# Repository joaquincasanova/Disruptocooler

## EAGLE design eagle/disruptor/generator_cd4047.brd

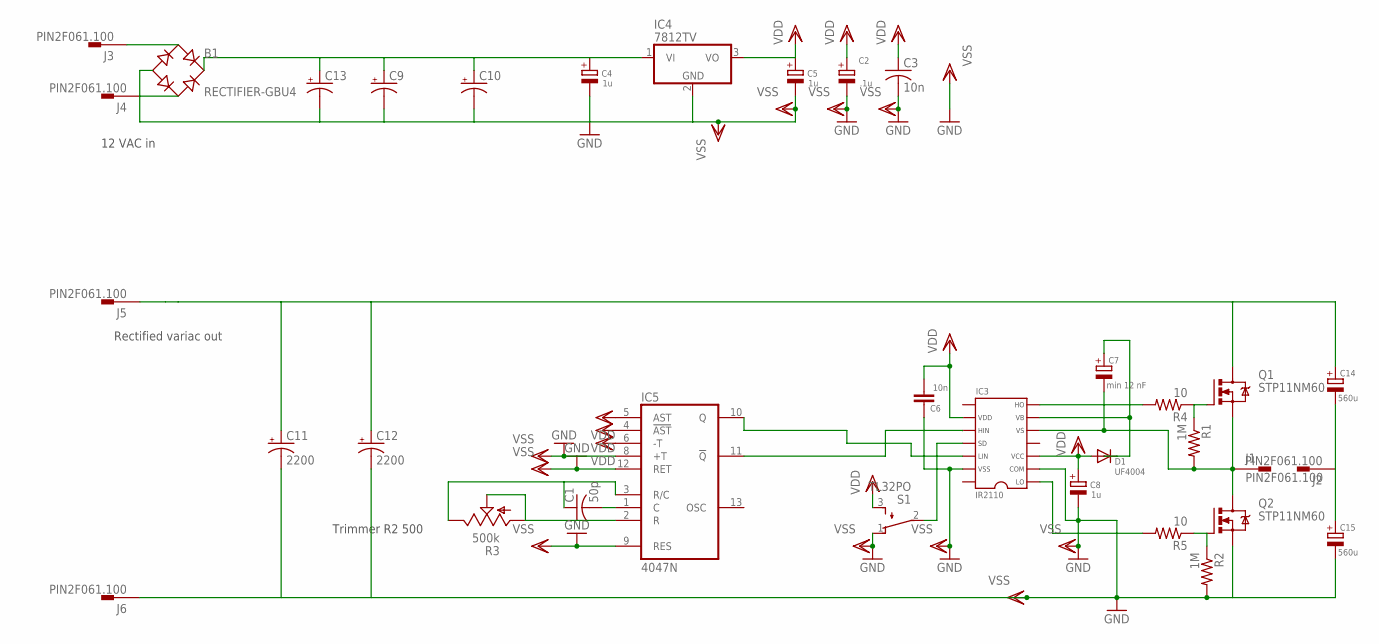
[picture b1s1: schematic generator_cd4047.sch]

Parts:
B1: RECTIFIER-GBU4; GBU4
C1: 50p; C075-042X103
C2: .1u; E5-8,5
C3: 10n; C075-042X103
C4, C5, C8: 1u; E5-8,5
C6: 10n; C075-052X106
C7: min 12 nF; E5-8,5
C9, C10, C13: CPOL-USE7.5-18; E7,5-18
C11, C12: 2200; EB35D
C14, C15: 560u; E7,5-16
D1: UF4004; D-7.5
IC3: IR2110; DIL14
IC4: 7812TV; TO220V
IC5: 4047N; DIL14
J1, J2, J3, J4, J5, J6: PIN2F061.100; F061.100
Q1, Q2: STP11NM60; TO220BV
R1, R2: 1M; 0207/10
R3: 500k; RJ9W
R4: 10; 0207/10
R5: 10; 0207/15
S1: TL32PO; TL3XPO

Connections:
HO: IC3.7, R4.2
LO: IC3.1, R5.2
unnamed: C7.+, D1.C, IC3.6
unnamed: IC5.2 (R), R3.A, R3.S
unnamed: C1.1, IC5.3 (R/C), R3.E
unnamed: C1.2, IC5.1 (C)
unnamed: IC3.12, IC5.10 (Q)
unnamed: C11.+, C12.+, C14.+, J5.A1, J5.A2, Q1.D
unnamed: B1.+, C4.+, C9.+, C10.+, C13.+, IC4.1 (VI)
unnamed: C14.-, C15.+, J2.A1, J2.A2
unnamed: B1.AC2, J4.A1, J4.A2
unnamed: B1.AC1, J3.A1, J3.A2
unnamed: Q2.G, R2.1, R5.1
unnamed: Q1.G, R1.1, R4.1
unnamed: IC3.10, IC5.11 (!Q)
unnamed: IC3.11, S1.2
TRANS: C7.-, IC3.5, J1.A1, J1.A2, Q1.S, Q2.D, R1.2
VDD: C2.+, C3.1, C5.+, C6.2, C8.+, D1.A, IC3.3, IC3.9, IC4.3 (VO), IC5.4 (!AST), IC5.5 (AST), IC5.6 (-T), IC5.14 (VDD), S1.3 (S)
VSS: B1.-, C2.-, C3.2, C4.-, C5.-, C6.1, C8.-, C9.-, C10.-, C11.-, C12.-, C13.-, C15.-, IC3.2, IC3.13, IC4.2 (GND), IC5.7 (VSS), IC5.8 (+T), IC5.9 (RES), IC5.12 (RET), J6.A1, J6.A2, Q2.S, R2.2, S1.1 (O)

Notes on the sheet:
12 VAC in
Rectified variac out
Trimmer R2 500

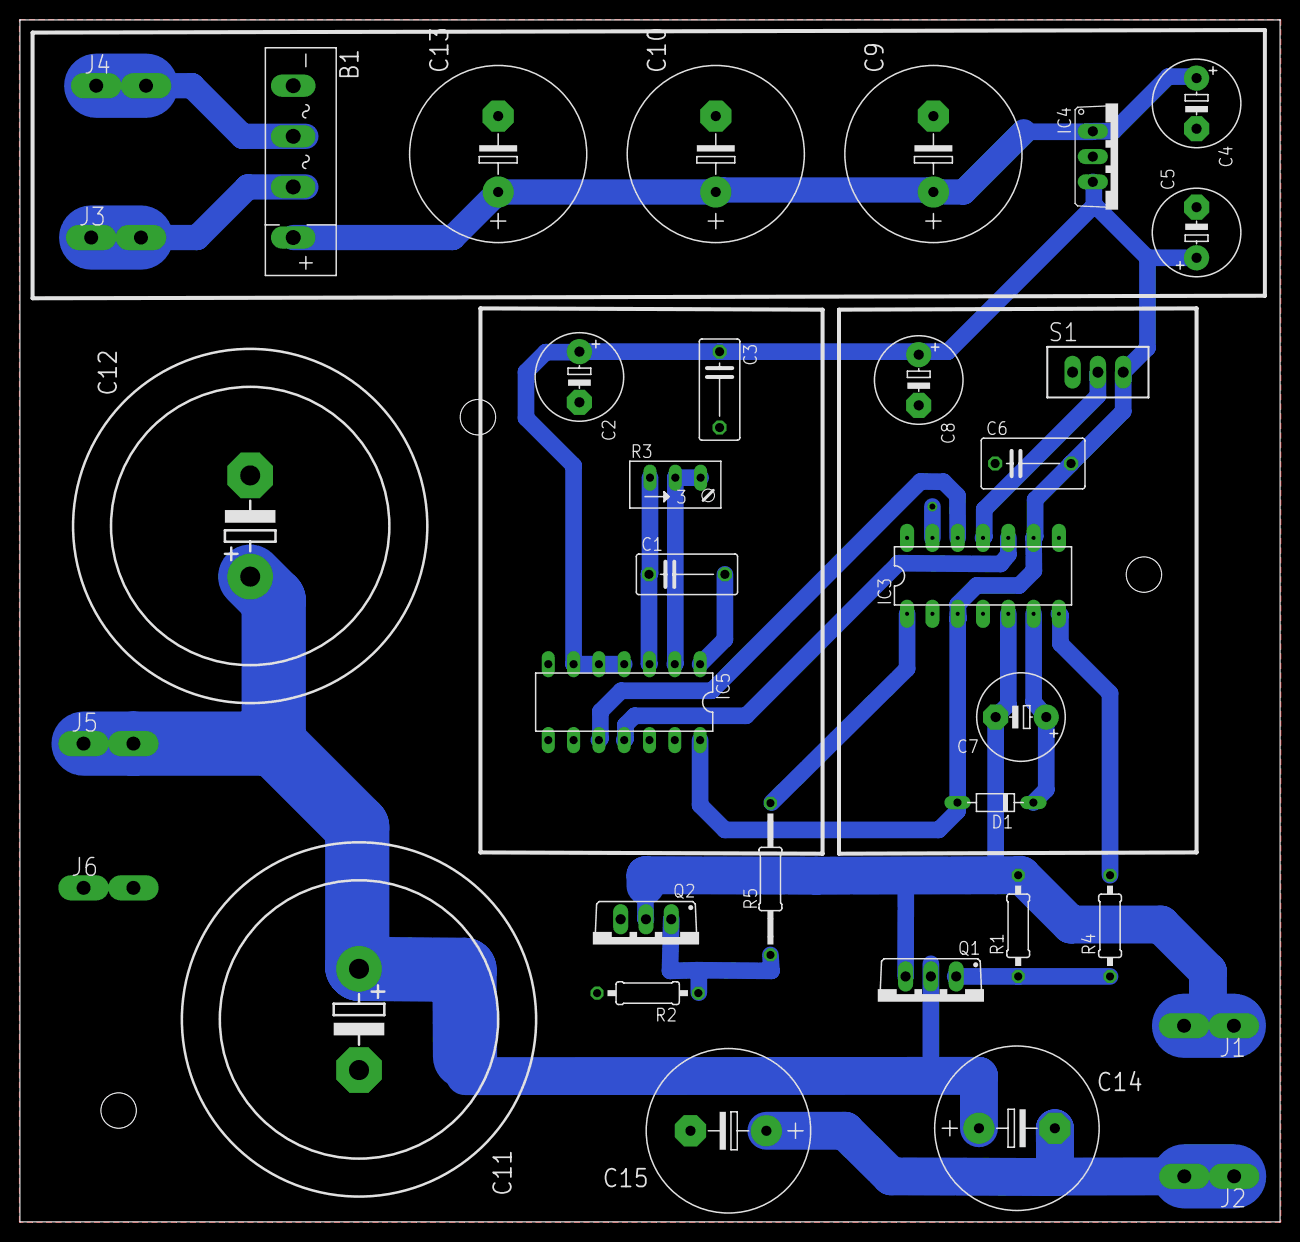
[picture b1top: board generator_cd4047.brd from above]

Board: 2 copper layers, 126.5 x 120.7 mm, 34 parts (0 on the bottom side), 19 nets.

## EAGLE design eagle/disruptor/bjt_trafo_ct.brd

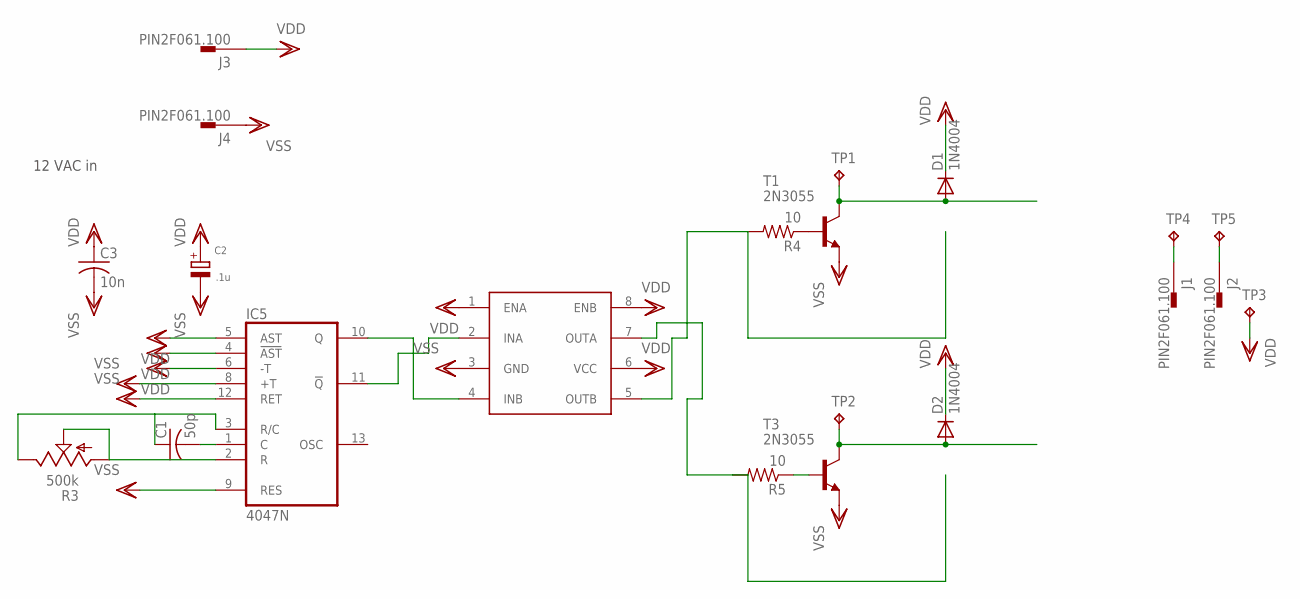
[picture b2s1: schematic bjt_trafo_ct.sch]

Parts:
C1: 50p; C075-042X103
C2: .1u; E5-8,5
C3: 10n; C075-042X103
D1, D2: 1N4004; DO41-10
IC5: 4047N; DIL14
J1, J2, J3, J4: PIN2F061.100; F061.100
R3: 500k; RJ9W
R4, R5: 10; 0207/10
T1, T3: 2N3055; TO3
TP1, TP2, TP3: TPPAD1-20Y; P1-20Y
TP4, TP5: TPPAD1-13Y; P1-13Y
U$1: UCC27425; DIL08

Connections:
unnamed: R5.2, U$1.7 (OUTA)
unnamed: IC5.2 (R), R3.A, R3.S
unnamed: C1.1, IC5.3 (R/C), R3.E
unnamed: C1.2, IC5.1 (C)
unnamed: D2.A, T3.C, T3.C/ (C), TP2.TP
unnamed: IC5.11 (!Q), U$1.2 (INA)
unnamed: J1.A1, J1.A2, TP4.TP
unnamed: J2.A1, J2.A2, TP5.TP
unnamed: R5.1, T3.B
unnamed: R4.1, T1.B
unnamed: R4.2, U$1.5 (OUTB)
unnamed: D1.A, T1.C, T1.C/ (C), TP1.TP
unnamed: IC5.10 (Q), U$1.4 (INB)
VDD: C2.+, C3.1, D1.C, D2.C, IC5.4 (!AST), IC5.5 (AST), IC5.6 (-T), IC5.14 (VDD), J3.A1, J3.A2, TP3.TP, U$1.1 (ENA), U$1.6 (VCC), U$1.8 (ENB)
VSS: C2.-, C3.2, IC5.7 (VSS), IC5.8 (+T), IC5.9 (RES), IC5.12 (RET), J4.A1, J4.A2, T1.E, T3.E, U$1.3 (GND)

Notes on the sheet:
12 VAC in

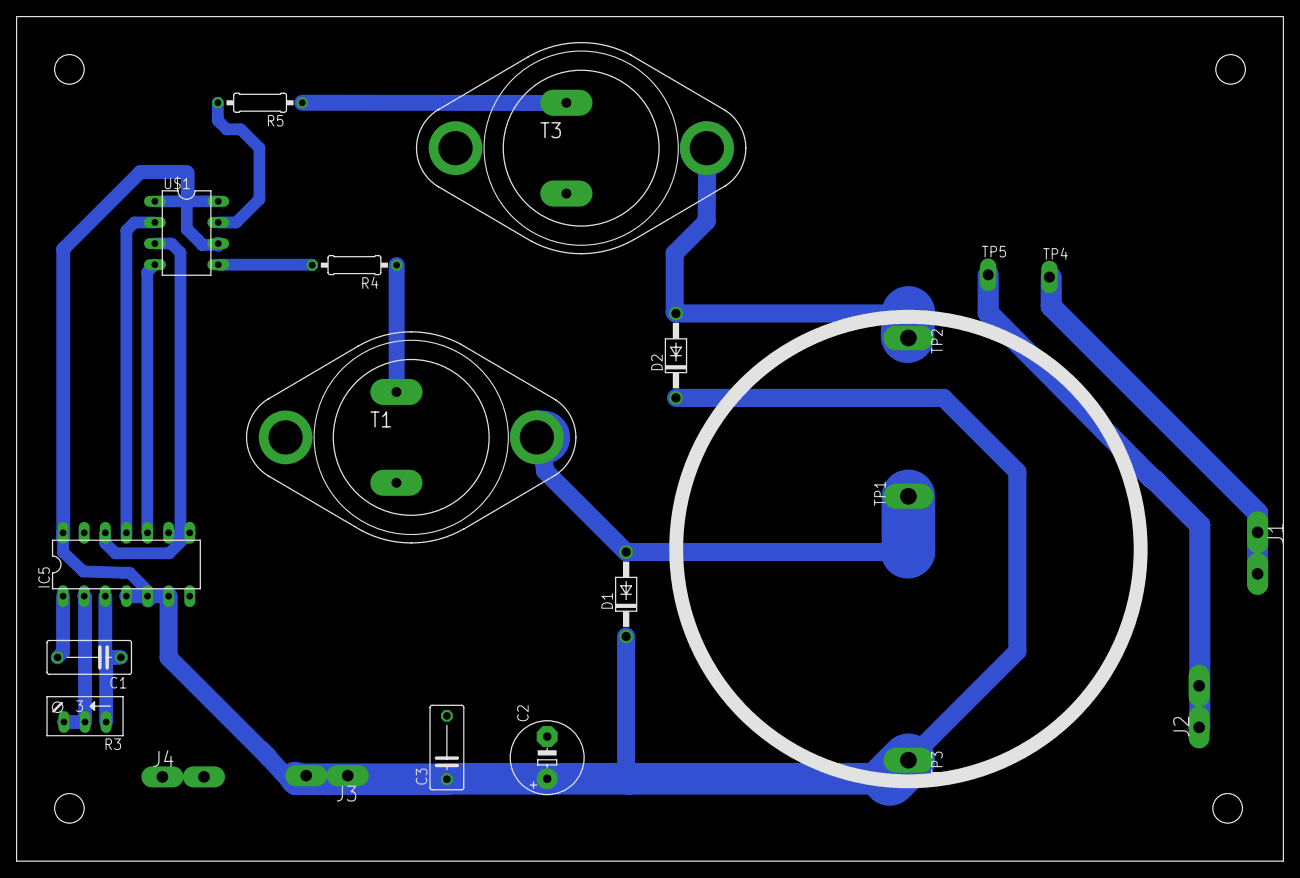
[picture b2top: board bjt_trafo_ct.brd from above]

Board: 2 copper layers, 152.4 x 101.6 mm, 21 parts (0 on the bottom side), 15 nets.

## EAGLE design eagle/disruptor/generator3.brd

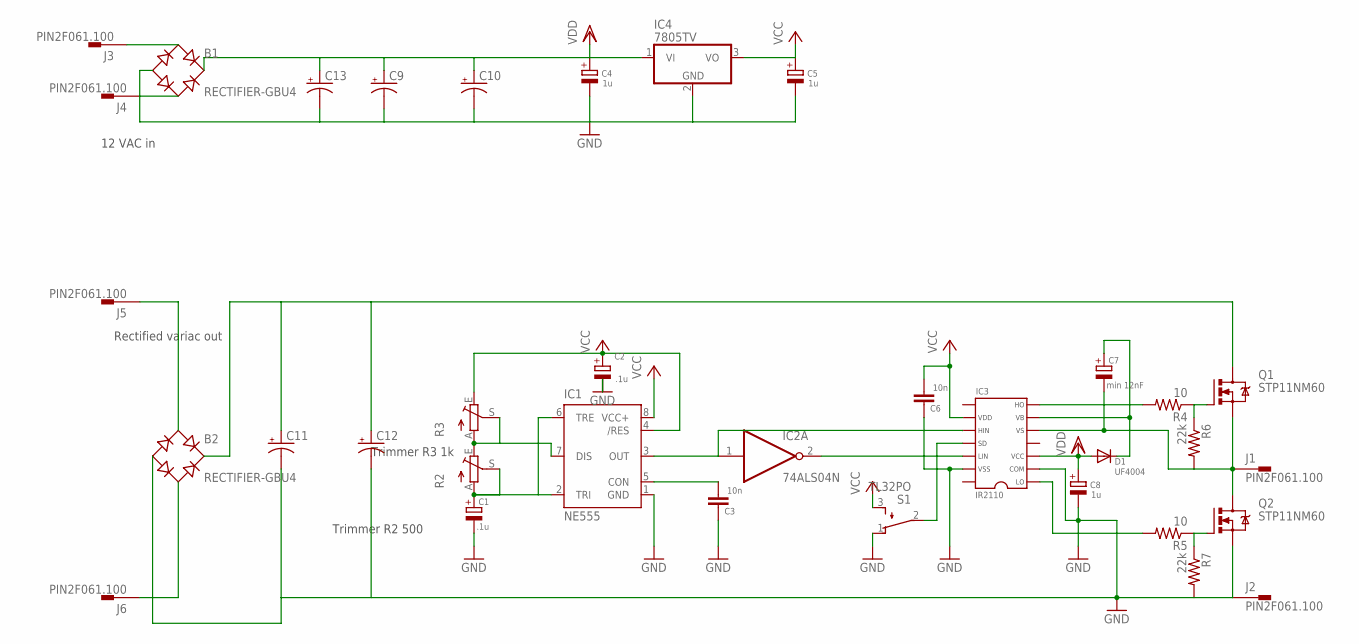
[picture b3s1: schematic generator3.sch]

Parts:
B1, B2: RECTIFIER-GBU4; GBU4
C1, C2: .1u; E5-8,5
C3, C6: 10n; C075-052X106
C4, C5, C8: 1u; E5-8,5
C7: min 12nF; E5-8,5
C9, C10, C13: CPOL-USE7.5-18; E7,5-18
C11, C12: CPOL-USE10-35; EB35D
D1: UF4004; D-7.5
IC1: NE555; DIL-08
IC2: 74ALS04N; DIL14
IC3: IR2110; DIL14
IC4: 7805TV; TO220V
J1, J2, J3, J4, J5, J6: PIN2F061.100; F061.100
Q1, Q2: STP11NM60; TO220BV
R2, R3: TRIM_EU-LI10; LI10
R4, R5: 10; 0207/10
R6, R7: 22k; 0207/10
S1: TL32PO; TL3XPO

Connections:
GND: B1.-, B2.-, C1.-, C2.-, C3.1, C4.-, C5.-, C6.1, C8.-, C9.-, C10.-, C11.-, C12.-, C13.-, IC1.1 (GND), IC2.7 (GND), IC3.2, IC3.13, IC4.2 (GND), J2.A1, J2.A2, Q2.S, R7.2, S1.1 (O)
HIN: IC1.3 (OUT), IC2.1 (I), IC3.10
HO: IC3.7, R4.2
LIN: IC2.2 (O), IC3.12
LO: IC3.1, R5.2
unnamed: C7.+, D1.C, IC3.6
unnamed: C1.+, IC1.2 (TRI), IC1.6 (TRE), R2.A, R2.S
unnamed: C3.2, IC1.5 (CON)
unnamed: B2.AC1, J5.A1, J5.A2
unnamed: B2.AC2, J6.A1, J6.A2
unnamed: B2.+, C11.+, C12.+, Q1.D
unnamed: IC1.7 (DIS), R2.E, R3.A, R3.S
unnamed: B1.AC2, J4.A1, J4.A2
unnamed: B1.AC1, J3.A1, J3.A2
unnamed: Q2.G, R5.1, R7.1
unnamed: Q1.G, R4.1, R6.1
unnamed: IC3.11, S1.2
TRANS: C7.-, IC3.5, J1.A1, J1.A2, Q1.S, Q2.D, R6.2
VCC: C2.+, C5.+, C6.2, IC1.4 (/RES), IC1.8 (VCC+), IC2.14 (VCC), IC3.9, IC4.3 (VO), R3.E, S1.3 (S)
VDD: B1.+, C4.+, C8.+, C9.+, C10.+, C13.+, D1.A, IC3.3, IC4.1 (VI)

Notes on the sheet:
12 VAC in
Rectified variac out
Trimmer R3 1k
Trimmer R2 500

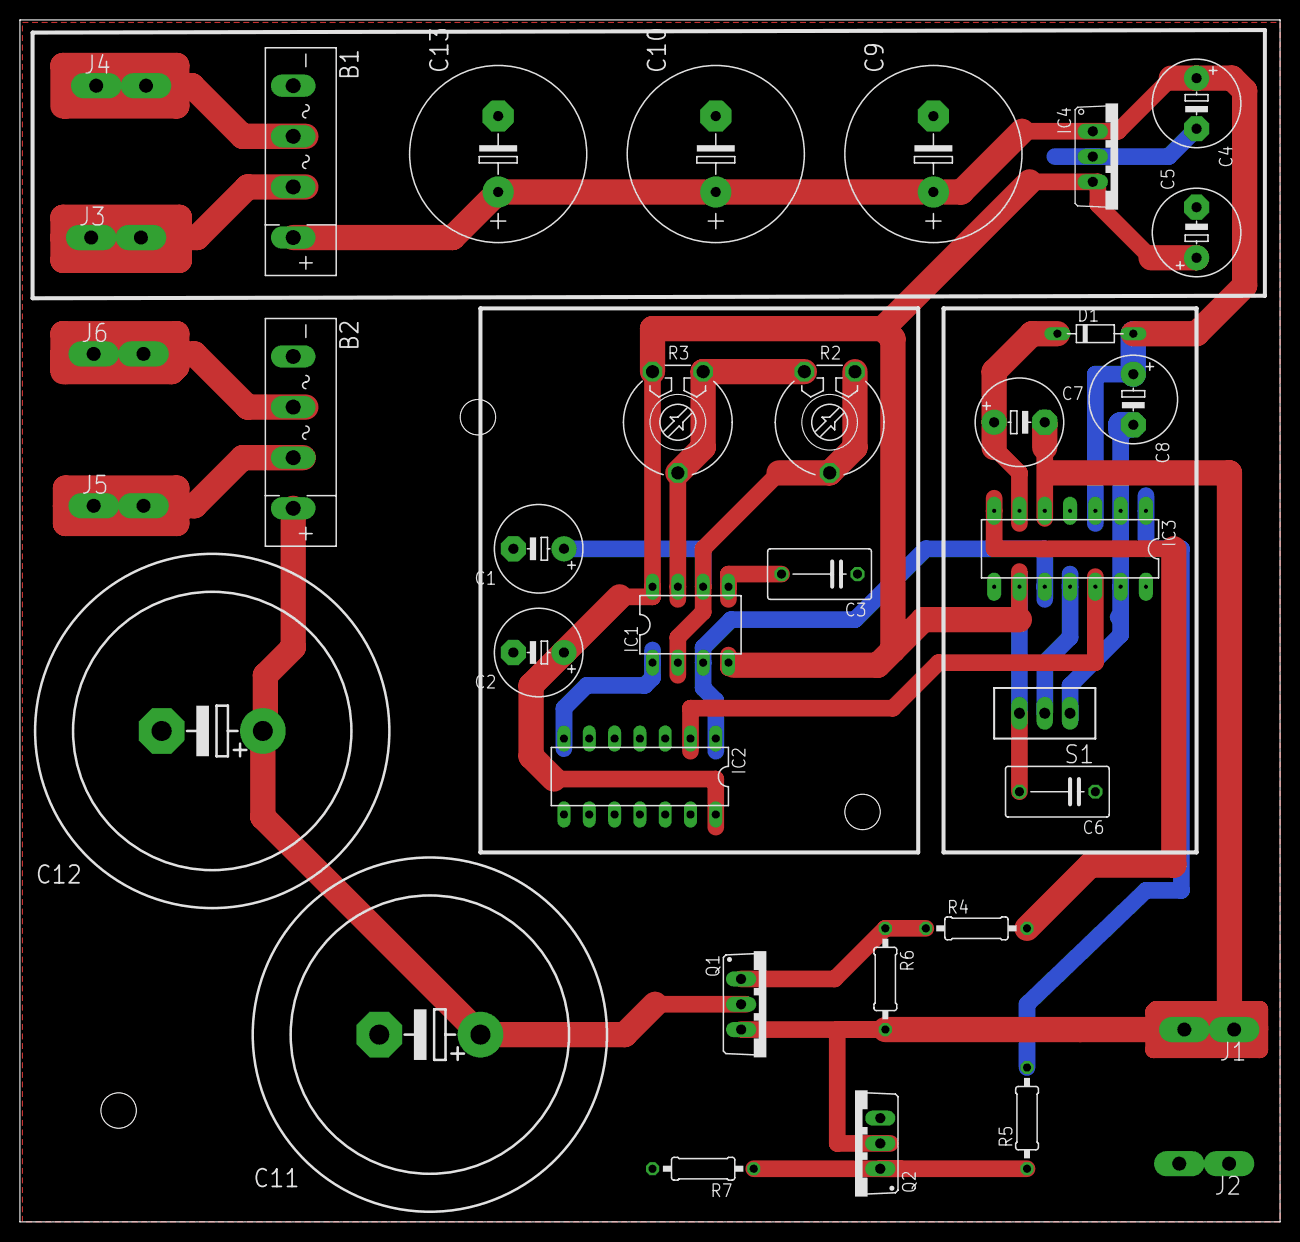
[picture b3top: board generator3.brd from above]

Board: 2 copper layers, 126.5 x 120.7 mm, 35 parts (0 on the bottom side), 20 nets.

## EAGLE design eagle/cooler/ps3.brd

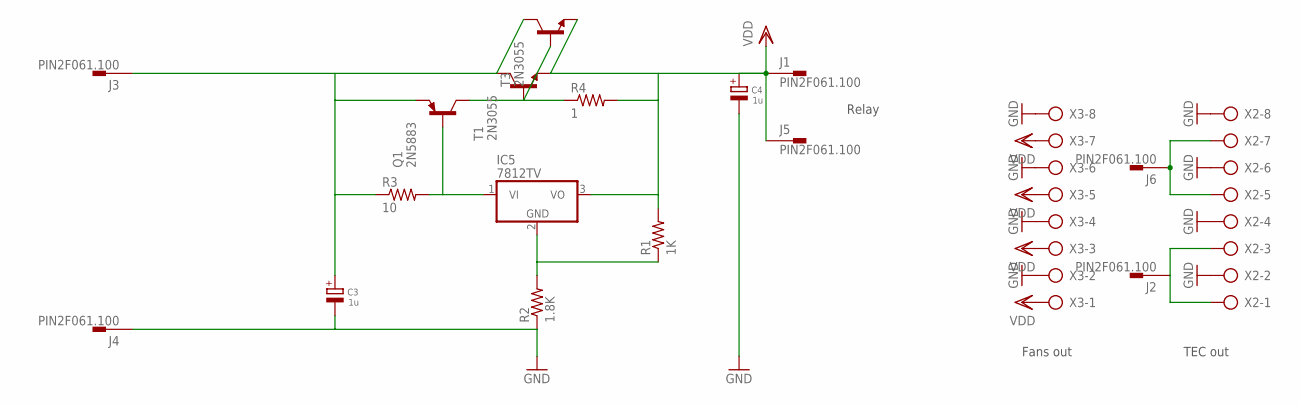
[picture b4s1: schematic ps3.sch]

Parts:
C3, C4: 1u; EB20D
IC5: 7812TV; TO220V
J1, J2, J3, J4, J5, J6: PIN2F061.100; F061.100
Q1: 2N5883; TO3
R1: 1K; 0207/15
R2: 1.8K; 0207/15
R3: 10; 0207/15
R4: 1; 0922/22
T1, T3: 2N3055; TO3
X2, X3: AK300/8

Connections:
B: Q1.C, Q1.C/ (C), R4.1, T1.B, T3.B
GND: C3.-, C4.-, J4.A1, J4.A2, R2.1, X2.2, X2.4, X2.6, X2.8, X3.2, X3.4, X3.6, X3.8
unnamed: IC5.2 (GND), R1.1, R2.2
TEC1: J2.A1, J2.A2, X2.1, X2.3
TEC2: J6.A1, J6.A2, X2.5, X2.7
VDD: C4.+, IC5.3 (VO), J1.A1, J1.A2, J5.A1, J5.A2, R1.2, R4.2, T1.E, T3.E, X3.1, X3.3, X3.5, X3.7
VI: IC5.1 (VI), Q1.B, R3.2
VIN: C3.+, J3.A1, J3.A2, Q1.E, R3.1, T1.C, T1.C/ (C), T3.C, T3.C/ (C)

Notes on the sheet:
Fans out
TEC out
Relay

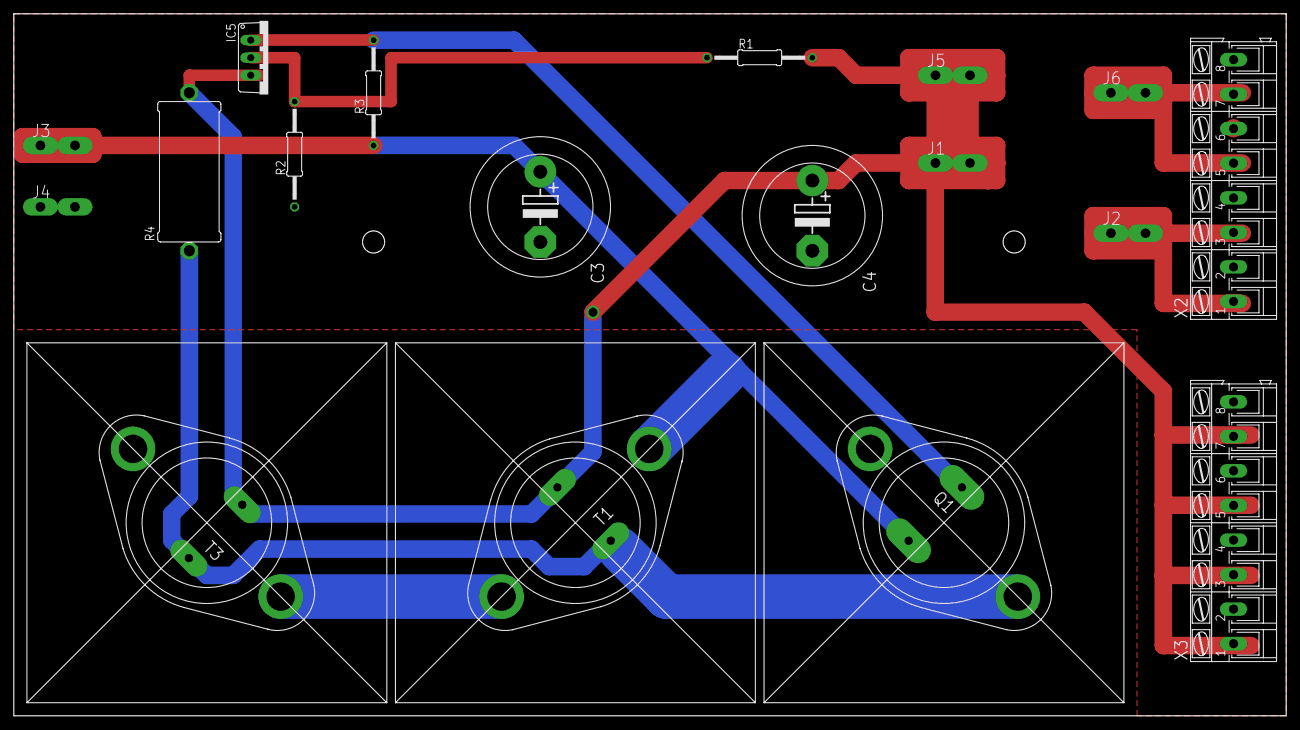
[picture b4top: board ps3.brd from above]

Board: 2 copper layers, 184.2 x 101.6 mm, 18 parts (0 on the bottom side), 8 nets.

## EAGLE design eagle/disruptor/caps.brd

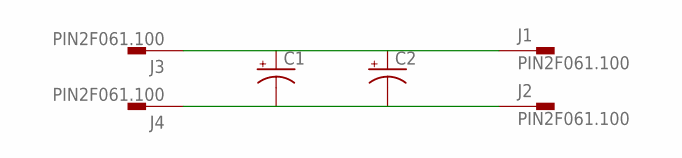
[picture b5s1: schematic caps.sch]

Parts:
C1, C2: CPOL-USE10-35; EB35D
J1, J2, J3, J4: PIN2F061.100; F061.100

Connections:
unnamed: C1.+, C2.+, J1.A1, J1.A2, J3.A1, J3.A2
unnamed: C1.-, C2.-, J2.A1, J2.A2, J4.A1, J4.A2

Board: 2 copper layers, 6 parts (0 on the bottom side), 2 nets, no tracks yet.

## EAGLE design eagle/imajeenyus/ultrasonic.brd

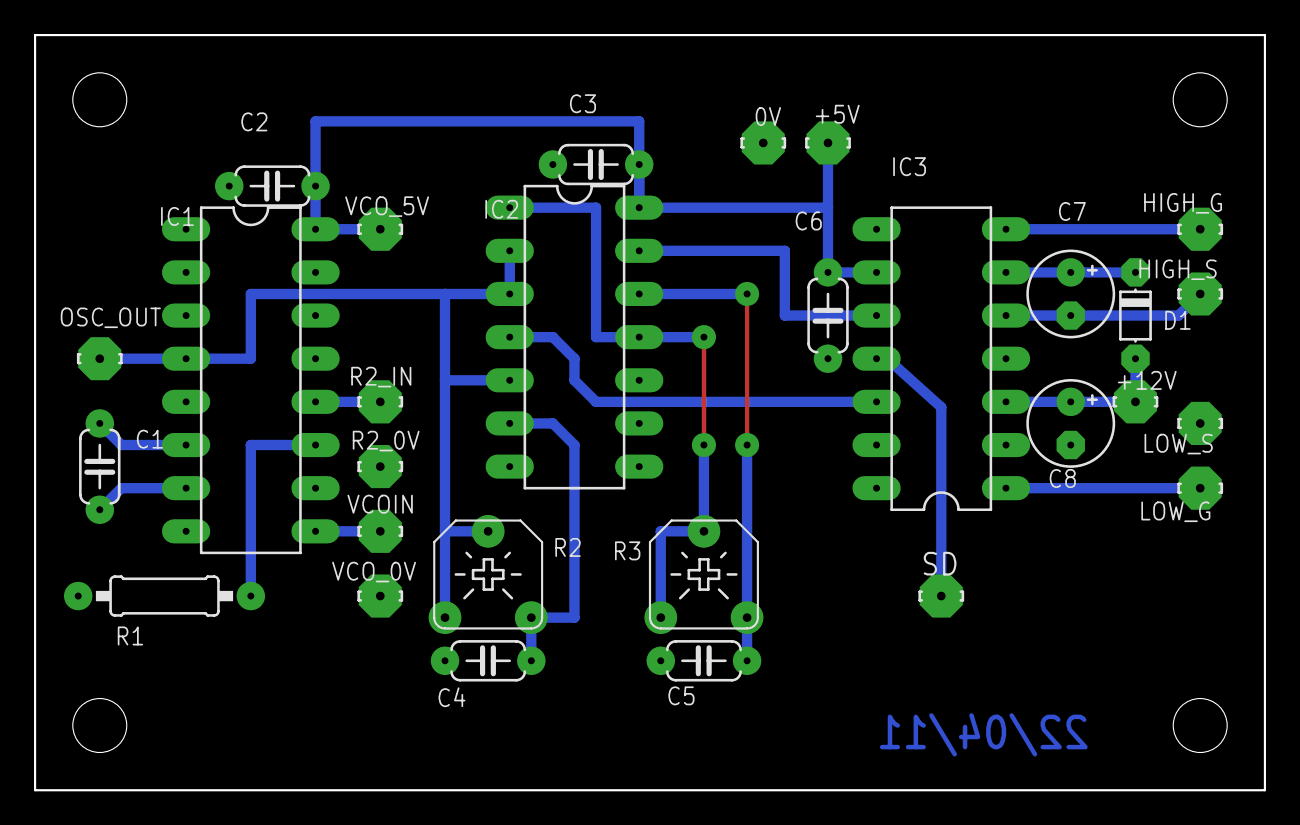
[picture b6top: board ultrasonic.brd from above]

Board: 2 copper layers, 72.4 x 44.5 mm, 29 parts (0 on the bottom side), 19 nets.

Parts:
0V: LSP10
+5V, +12V: LSP10
C1: 10n; C050-024X044
C2, C3, C6: 100n; C050-024X044
C4, C5: 47p; C050-024X044
C7, C8: 2u2; E2,5-5
D1: UF4004; D-5
HIGH_G: LSP10
HIGH_S: LSP10
IC1: 74HC4046N; DIL16
IC2: 7402N; DIL14
IC3: IR2110; DIL14
LOW_G: LSP10
LOW_S: LSP10
OSC_OUT: LSP10
R1: 200k; 0207/10
R2, R3: 10k; RTRIMCA6V
R2_0V, R2_IN: LSP10
SD: LSP10
VCOIN: LSP10
VCO_0V, VCO_5V: LSP10

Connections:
0V: 0V.MP, C2.2, C3.2, C4.2, C5.2, C6.2, C8.-, IC1.5, IC1.8, IC2.7, IC2.8, IC2.9, IC3.2, IC3.13, LOW_S.MP, R1.1, R2_0V.MP, VCO_0V.MP
+5V: +5V.MP, C2.1, C3.1, C6.1, IC1.16, IC2.14, IC3.9, VCO_5V.MP
+12V: +12V.MP, C8.+, D1.A, IC3.3
unnamed: C7.+, D1.C, IC3.6
unnamed: IC2.13, IC3.10
unnamed: IC2.4, IC3.12
unnamed: IC2.1, IC2.11, R3.A, R3.S
unnamed: IC3.1, LOW_G.MP
unnamed: C7.-, HIGH_S.MP, IC3.5
unnamed: C4.1, IC2.6, R2.E
unnamed: HIGH_G.MP, IC3.7
unnamed: IC1.4, IC2.2, IC2.3, IC2.5, OSC_OUT.MP, R2.A, R2.S
unnamed: C5.1, IC2.12, R3.E
unnamed: IC1.9, VCOIN.MP
unnamed: C1.1, IC1.6
unnamed: C1.2, IC1.7
unnamed: IC1.11, R1.2
unnamed: IC1.12, R2_IN.MP
unnamed: IC3.11, SD.MP

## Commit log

2014-08-21 :confetti_ball: Added .gitattributes & .gitignore files
2014-08-21 first
    first
2014-08-22 change power on gen board
    change power on gen board
2014-08-25 layouts
2014-08-25 layout
2014-08-29 schematics auber
2014-08-29 auber
2014-08-30 gnd top
2014-09-04 etched
2014-09-05 ftkvjg7
2014-09-11 rev2
2014-09-17 final tweaks on ps3
2014-09-25 gen3
2014-09-26 gen4
2014-09-26 gen4b
2014-09-27 generator 4 is the correct way.
2014-09-27 use generator 4
2014-09-28 gen 4 board layout done.
2014-09-29 final board
2014-10-01 BETTER VREG, HALF BRIDGE
2014-10-02 beefier cap values
2015-07-01 pre-round 2
2015-12-14 wryqedx
